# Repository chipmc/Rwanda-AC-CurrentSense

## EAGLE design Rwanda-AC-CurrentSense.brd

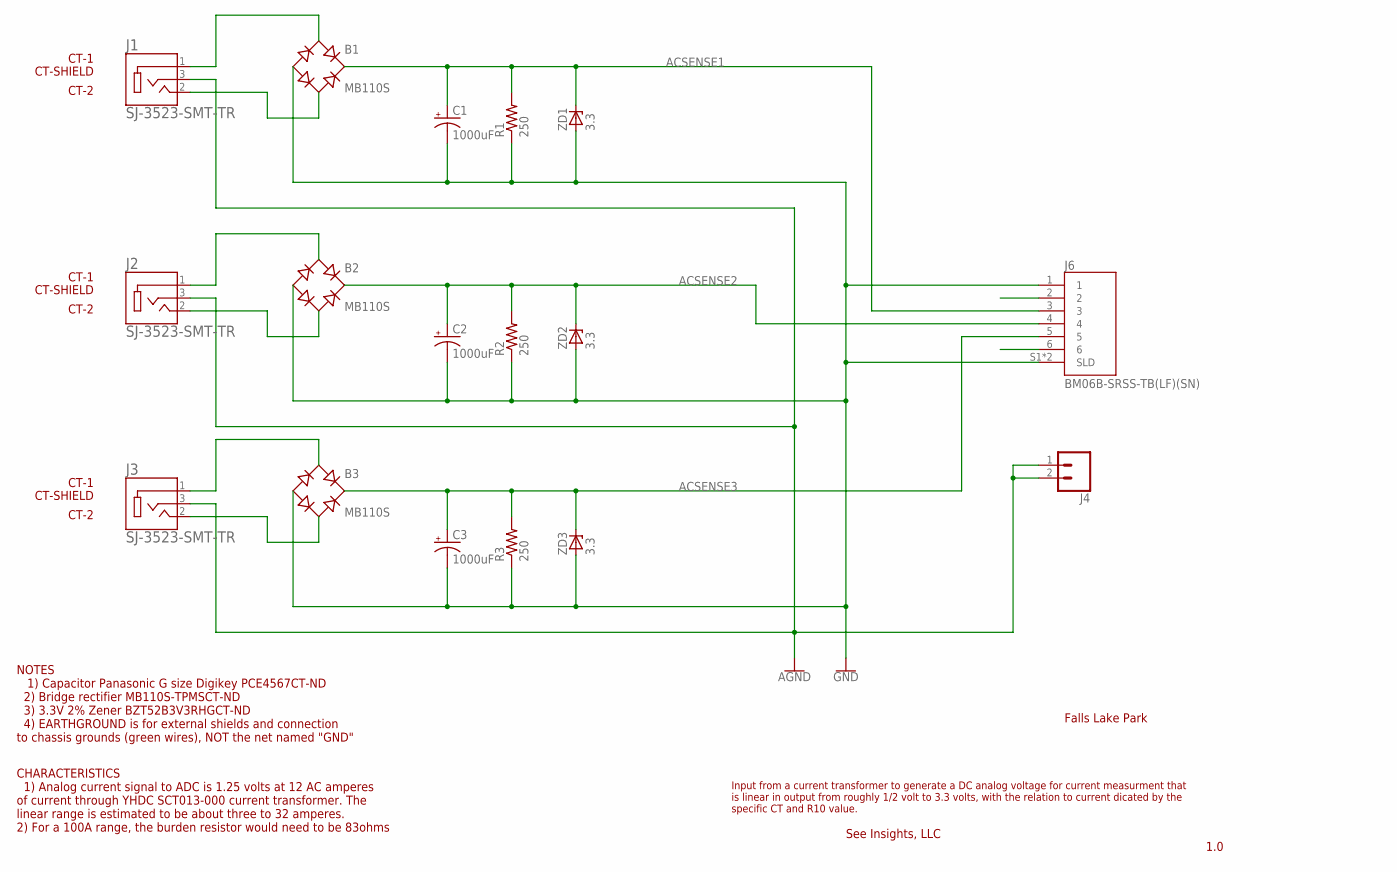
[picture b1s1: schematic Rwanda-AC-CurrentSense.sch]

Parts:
B1: MB110S; SOIC-4; MPN MB1S
B2, B3: MB110S; SOIC-4
C1, C2, C3: 1000uF; PANASONIC_G
J1, J2, J3: SJ-3523-SMT-TR; CUI_SJ-3523-SMT-TR
J4: CONN_02; 1X02
J6: BM06B-SRSS-TB(LF)(SN); JST_BM06B-SRSS-TB(LF)(SN)
R1, R2: 250; M1206
R3: 250; M1206; MPN CR1206-FX-2202ELF
ZD1, ZD2: 3.3; SOD123
ZD3: 3.3; SOD123; MPN BZT52B3V3 RHG

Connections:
ACSENSE1: B1.+, C1.+, J6.3, R1.2, ZD1.C
ACSENSE2: B2.+, C2.+, J6.4, R2.2, ZD2.C
ACSENSE3: B3.+, C3.+, J6.5, R3.2, ZD3.C
GND: B1.-, B2.-, B3.-, C1.-, C2.-, C3.-, J6.1, J6.S1 (SLD), J6.S2 (SLD), R1.1, R2.1, R3.1, ZD1.A, ZD2.A, ZD3.A
unnamed: B2.~2 (AC2), J2.2
unnamed: B2.~1 (AC1), J2.1
unnamed: B1.~2 (AC2), J1.2
unnamed: B1.~1 (AC1), J1.1
unnamed: B3.~2 (AC2), J3.2
unnamed: B3.~1 (AC1), J3.1
SHEILD: J1.3, J2.3, J3.3, J4.1, J4.2

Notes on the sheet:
1.0
See Insights, LLC
Input from a current transformer to generate a DC analog voltage for current measurment that is linear in output from roughly 1/2 volt to 3.3 volts, with the relation to current dicated by the specific CT and R10 value.
Falls Lake Park
NOTES 1) Capacitor Panasonic G size Digikey PCE4567CT-ND 2) Bridge rectifier MB110S-TPMSCT-ND 3) 3.3V 2% Zener BZT52B3V3RHGCT-ND 4) EARTHGROUND is for external shields and connection to chassis grounds (green wires), NOT the net named "GND"
CHARACTERISTICS 1) Analog current signal to ADC is 1.25 volts at 12 AC amperes of current through YHDC SCT013-000 current transformer. The linear range is estimated to be about three to 32 amperes. 2) For a 100A range, the burden resistor would need to be 83ohms
CT-1
CT-2
CT-SHIELD

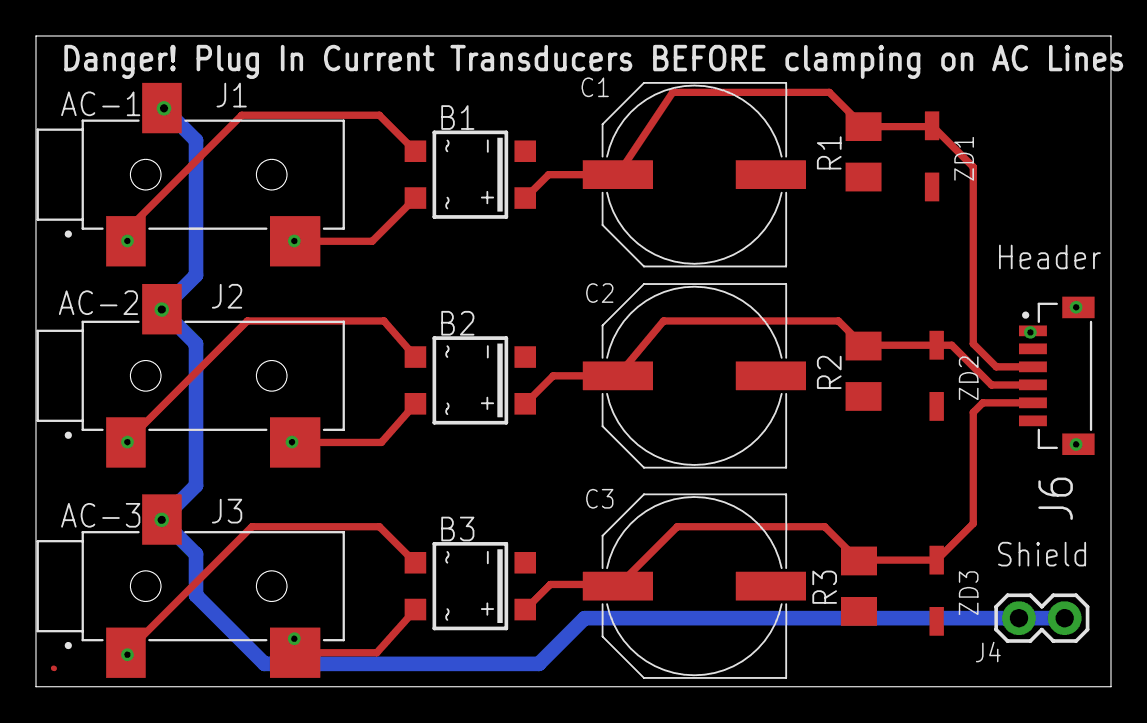
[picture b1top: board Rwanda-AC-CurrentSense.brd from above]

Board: 2 copper layers, 59.7 x 36.2 mm, 17 parts (0 on the bottom side), 11 nets.

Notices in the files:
parts and their libraries:
SparkFun-Connectors: Licensing: Creative Commons ShareAlike 4.0 International - https://creativecommons.org/licenses/by-sa/4.0
PJS: Author, license:
